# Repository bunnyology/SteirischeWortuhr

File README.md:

# SteirischeWortuhr
Wortuhr im steirischen Dialekt (Arduino/3D Druck)

Diese Wortuhr zeigt die aktuelle Uhrzeit auf Steirisch an. Dabei sind nicht nur die Zahlenworte in Mundart gehalten, sondern auch die eigentümliche- und für Nicht-Steirer wohl auch verwirrende Angabe der Uhrzeit ist dem lokalen Sprachgebrauch nachempfunden (14 Uhr 15 wird z.B. als "viertel Drei (!)" angegeben.

# Elektronik
Gesteuert wird die Uhr mit einem Arduino Nano und ein DCF-77 Funkuhrempfänger stellt die Zeit automatisch sekundengenau ein.

Sollte man nicht im 1500km Umkreis von Frankfurt wohnen, kann diese Antenne auch eingespart, und die Uhrzeit mit der Taste eingestellt werden.

Ich habe versucht, die Elektronik so simpel wie nur Möglich zu halten und auch auf LED Treiber verzichtet. Der Arduino treibt die eingesetzten 5mm LEDs ohne weitere Elektronik. Dafür habe ich Ultrabright LEDs eingesetzt (ca. 14000 mcd bei 20mA) und treibe diese mit 4mA um unter den Limits des Microcontrollers u bleiben. Da jedoch diese Ultrabright LEDs meistens einen sehr engen Abstrahlwinkel haben (was zu einer unregelmäßigen Ausleuchtung führen würde), habe ich die Köpfe der LEDs flach abgeschliffen.

Um die "Produktion" zu vereinfachen, habe ich eine eigene Platine fertigen lassen. Die KiCAD Schematics und PCB Daten sind hier herunterladbar, ebenso die Gerber Daten für die Platinenproduktion. Will man aber nur eine einzige Uhr herstellen, kann die Elektronik auch ganz einfach nur verkabelt werden. Der Verdratungsplan ist recht simpel:

# Bedienung der Wortuhr
Die Uhr wird über ein 12V Netzteil mit Strom versorgt und startet beim Einstecken des Netzteilsteckers automatisch. Wird während des Einschaltens der Taster gedrückt, startet der Selbstcheck (die Uhr läuft einen 12 Stunden Zyklus schnell durch).

Solange kein Zeitpacket empfangen wird blinkt "GLEI" im Sekundentakt. Wird ein Synchronisationssignal erkannt (jede volle Minute), erhöht sich die Blinkgeschindigkeit (500ms). Sobald die Zeitinformation empfangen wird (ab Sekunde 20), verdoppelt sich die Blinkgeschwindigkeit noch einmal, bis die gesamte Uhrzeit eingelesen wurde. Dann wird die empfangene Uhrzeit angezeigt.

Hinweis: Das DCF-77 Signal ist recht schwach, und daher die Ausrichtung der Antenne wichtig. Die Uhr solle für einen guten Empfang nach Frankfurt ausgerichtet sein (Anzeige in oder gegen Blickrichtung Frankfurt).

Ist ein Empfang nicht möglich, kann die Uhrzeit auch über den Taster eingestellt werden. Dazu muss der Taster 3 Sekunden gedrückt gehalten werden. "ES IS" fängt dann zu blinken an und mit weiteren kurzen Tastendrucks kann die Uhrzeit in 5 Minuten Schritten eingestellt werden. Erneutes 3 Sekunden Drücken speichert die Uhrzeit und "ES IS" leuchtet wieder konstant.
Sobald ein Zeitpacket empfangen wird, synchronisiert sich die Uhrzeit wieder automatisch.

Die Helligkeit der Anzeige kann in vier Stufen durch kurzes Drücken des Tasters eingestellt werden.

# 3D Druck

Die 3D Modelle und Druckdateien können hier heruntergeladen werden:

https://www.prusaprinters.org/prints/44454-steirische-wort-uhr-styrian-dialect-word-clock

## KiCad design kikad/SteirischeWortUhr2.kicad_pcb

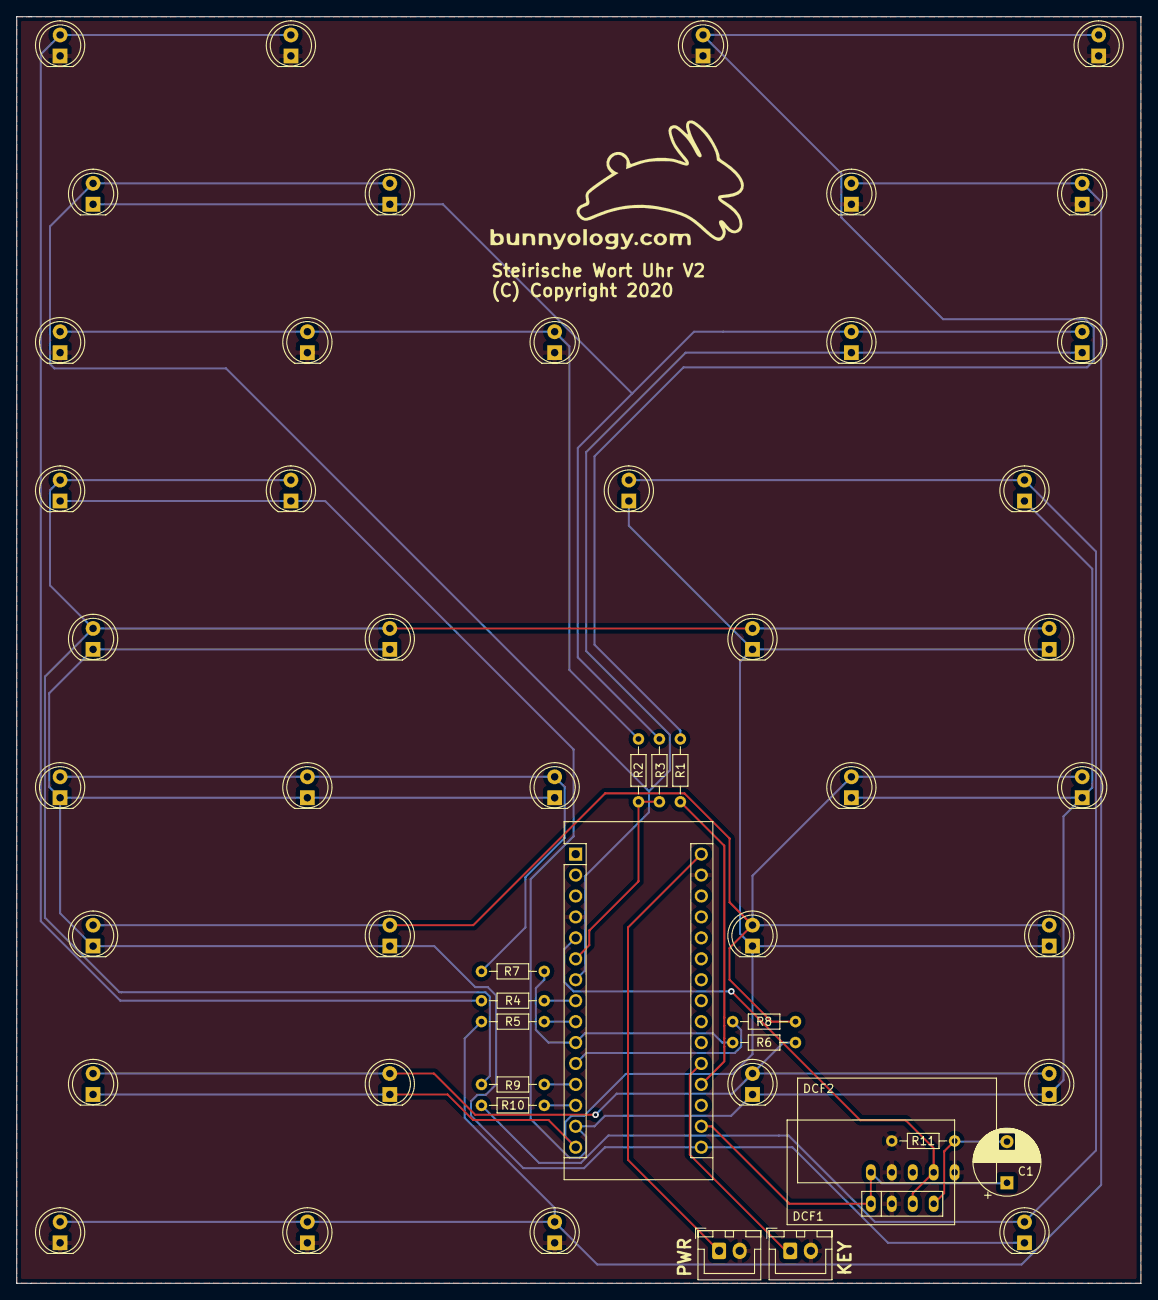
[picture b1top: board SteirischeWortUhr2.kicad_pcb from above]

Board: 2 copper layers, 136.4 x 153.7 mm, 55 parts (0 on the bottom side), 28 nets.

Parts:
ArduinoNanoV3: Arduino_Nano_v3.x; Arduino_Nano
C1: 10u; CP_Radial_D8.0mm_P5.00mm
DCF1: Pollin-DCF1; Pollin-DFC77
DCF2: MAS6180-DCF77; MAS6180B1-DFC77
J1PWR1, J2KEY1: JST-XH-A02; JST_XH_B2B-XH-A_1x02_P2.50mm_Vertical
LED_ANS_1: 00430340/1; LED_D5.0mm_IRGrey
LED_DREI4TL_1, LED_DREI4TL_2: 00430340/1; LED_D5.0mm_IRGrey
LED_DREI_1, LED_DREI_2: 00430340/1; LED_D5.0mm_IRGrey
LED_ESIS_1, LED_ESIS_2: 00430340/1; LED_D5.0mm_IRGrey
LED_FÜNFE_1, LED_FÜNFE_2: 00430340/1; LED_D5.0mm_IRGrey
LED_GLEI_1, LED_GLEI_2: 00430340/1; LED_D5.0mm_IRGrey
LED_HOLBA_1, LED_HOLBA_2: 00430340/1; LED_D5.0mm_IRGrey
LED_NAINE_1, LED_NAINE_2: 00430340/1; LED_D5.0mm_IRGrey
LED_OCHTE_1, LED_OCHTE_2: 00430340/1; LED_D5.0mm_IRGrey
LED_SCHO_1, LED_SCHO_2: 00430340/1; LED_D5.0mm_IRGrey
LED_SEXE_1, LED_SEXE_2: 00430340/1; LED_D5.0mm_IRGrey
LED_SIEBN_1, LED_SIEBN_2: 00430340/1; LED_D5.0mm_IRGrey
LED_VIERE_1, LED_VIERE_2: 00430340/1; LED_D5.0mm_IRGrey
LED_VIERTL_1, LED_VIERTL_2, LED_VIERTL_3: 00430340/1; LED_D5.0mm_IRGrey
LED_VUABEI_1, LED_VUABEI_2, LED_VUABEI_3: 00430340/1; LED_D5.0mm_IRGrey
LED_ZEHNE_1, LED_ZEHNE_2: 00430340/1; LED_D5.0mm_IRGrey
LED_ZWA_1: 00430340/1; LED_D5.0mm_IRGrey
LED_ZWÖLFE_1, LED_ZWÖLFE_2, LED_ZWÖLFE_3: 00430340/1; LED_D5.0mm_IRGrey
LED_ÖFE_1: 00430340/1; LED_D5.0mm_IRGrey
R1, R3, R4, R6, R8, R9: 220; R_Axial_DIN0204_L3.6mm_D1.6mm_P7.62mm_Horizontal
R2, R7: 150; R_Axial_DIN0204_L3.6mm_D1.6mm_P7.62mm_Horizontal
R5: 100; R_Axial_DIN0204_L3.6mm_D1.6mm_P7.62mm_Horizontal
R10: 330; R_Axial_DIN0204_L3.6mm_D1.6mm_P7.62mm_Horizontal
R11: 10k; R_Axial_DIN0204_L3.6mm_D1.6mm_P7.62mm_Horizontal

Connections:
+3V3: ArduinoNanoV3.17, C1.1, DCF1.1, DCF2.1
GND: ArduinoNanoV3.4, ArduinoNanoV3.29, DCF1.2, DCF2.2, DCF2.5, J1PWR1.2, J2KEY1.2, LED_ESIS_1.1, LED_ESIS_2.1, LED_GLEI_1.1, LED_GLEI_2.1, LED_SCHO_1.1, LED_SCHO_2.1, LED_VIERTL_1.1, LED_VIERTL_2.1, LED_VIERTL_3.1, LED_VUABEI_1.1, LED_VUABEI_2.1, LED_VUABEI_3.1, R11.1
unnamed: ArduinoNanoV3.5, DCF1.3, DCF2.4
unnamed: ArduinoNanoV3.6, R2.1, R3.1
unnamed: ArduinoNanoV3.7, LED_DREI4TL_1.1, LED_DREI4TL_2.1, LED_HOLBA_1.2, LED_HOLBA_2.2
unnamed: ArduinoNanoV3.8, R4.1
unnamed: ArduinoNanoV3.9, R5.2
unnamed: ArduinoNanoV3.10, R6.1, R7.1
unnamed: ArduinoNanoV3.11, R8.1
unnamed: ArduinoNanoV3.12, R9.1
unnamed: ArduinoNanoV3.13, R10.1
unnamed: ArduinoNanoV3.14, LED_ANS_1.1, LED_DREI_1.1, LED_DREI_2.1, LED_SEXE_1.1, LED_SEXE_2.1, LED_ZEHNE_1.1, LED_ZEHNE_2.1
unnamed: ArduinoNanoV3.15, LED_OCHTE_1.1, LED_OCHTE_2.1, LED_SIEBN_1.1, LED_SIEBN_2.1, LED_VIERE_1.1, LED_VIERE_2.1, LED_ZWA_1.1
unnamed: ArduinoNanoV3.16, LED_FÜNFE_1.1, LED_FÜNFE_2.1, LED_NAINE_1.1, LED_NAINE_2.1, LED_ZWÖLFE_1.1, LED_ZWÖLFE_2.1, LED_ZWÖLFE_3.1, LED_ÖFE_1.1
unnamed: ArduinoNanoV3.19, R1.1
unnamed: ArduinoNanoV3.20, J2KEY1.1
unnamed: ArduinoNanoV3.30, J1PWR1.1
unnamed: C1.2, DCF1.4, R11.2
unnamed: LED_ANS_1.2, LED_ZWA_1.2, LED_ÖFE_1.2, R10.2
unnamed: LED_DREI4TL_1.2, LED_DREI4TL_2.2, LED_HOLBA_1.1, LED_HOLBA_2.1, R3.2
unnamed: LED_DREI_1.2, LED_DREI_2.2, LED_FÜNFE_1.2, LED_FÜNFE_2.2, LED_VIERE_1.2, LED_VIERE_2.2, R9.2
unnamed: LED_ESIS_1.2, LED_ESIS_2.2, R1.2
unnamed: LED_GLEI_1.2, LED_GLEI_2.2, R4.2
unnamed: LED_NAINE_1.2, LED_NAINE_2.2, LED_OCHTE_1.2, LED_OCHTE_2.2, LED_SEXE_1.2, LED_SEXE_2.2, R8.2
unnamed: LED_SCHO_1.2, LED_SCHO_2.2, LED_VUABEI_1.2, LED_VUABEI_2.2, LED_VUABEI_3.2, R5.1
unnamed: LED_SIEBN_1.2, LED_SIEBN_2.2, LED_ZEHNE_1.2, LED_ZEHNE_2.2, R6.2
unnamed: LED_VIERTL_1.2, LED_VIERTL_2.2, LED_VIERTL_3.2, R2.2
unnamed: LED_ZWÖLFE_1.2, LED_ZWÖLFE_2.2, LED_ZWÖLFE_3.2, R7.2

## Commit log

2021-01-04 Create null

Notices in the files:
kikad/SteirischeWortUhr2.kicad_pcb:
(C) Copyright 2020
